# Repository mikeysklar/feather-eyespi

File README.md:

# feather-eyespi

A plus-size FeatherWing base board that accepts an Adafruit Feather and breaks out an EYESPI connector for eInk and TFT displays.

Working with a lot of eInk and TFT displays means constantly re-wiring the EYESPI cable. This adapter cuts out that step — plug the Feather in, plug the display in, done. Single-sided board with minimal routing to keep assembly straightforward.

### BOM

| Part | Package | 
|------|---------|
| EYESPI | 18-pin FPC connector 
| headers | Female 2.54mm vertical SMT 
| Resistor, 0Ω | 0805 

### EYESPI Connected to eInk

---

### Assembled

---

### 18-pin FPC 

---

### Metal Business Card Stencil

---

### Finish PCB Silk / Mask Etched

---

### Wiring

| Feather Pin | Net | EYESPI Pin | Function |
|-------------|-----|-----------|----------|
| SCK | sck | 15 | SPI clock |
| MOSI | mosi | 14 | SPI data out |
| MISO | miso | 13 | SPI data in |
| D11 | rst | 11 | Reset |
| D10 | dc | 12 | Data / Command |
| D12 | busy | 3 | Busy / Ready |
| D9 | tcs | 10 | TCS chip select |
| 3V3 | 3v3 | 18 | 3.3V power |
| GND | gnd | 16 | Ground |

---

### Fiber Laser Etched PCB 

---

### Backside board ID

---

### KiCAD PCB

---

## License

This project is licensed under the GNU General Public License v3.0 — see the [LICENSE](LICENSE) file for details.

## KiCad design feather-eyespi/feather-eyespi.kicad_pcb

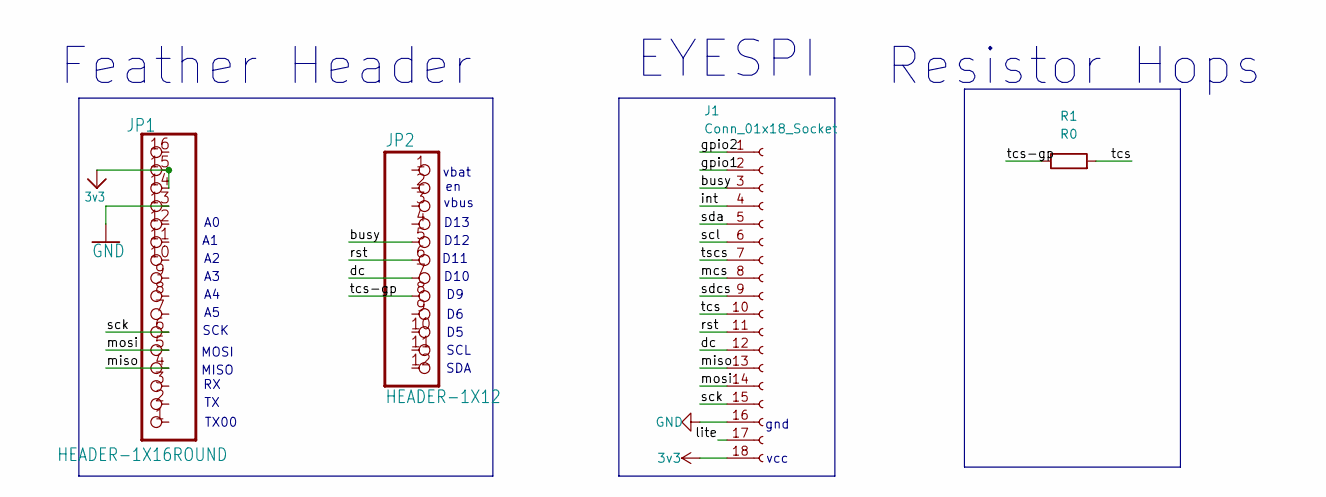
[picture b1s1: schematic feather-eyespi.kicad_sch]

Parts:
J1: Conn_01x18_Socket; Hirose_FH12-18S-0.5SH_1x18-1MP_P0.50mm_Horizontal
JP1: HEADER-1X16ROUND; PinHeader_1x16_P2.54mm_Vertical_SMD_Pin1Left
JP2: HEADER-1X12; PinSocket_1x12_P2.54mm_Vertical_SMD_Pin1Left
R1: R0; R_0805_2012Metric_Pad1.20x1.40mm_HandSolder

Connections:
3v3: J1.18, JP1.14, JP1.15
/busy: J1.3, JP2.5
/dc: J1.12, JP2.7
/gpio1: J1.2
/gpio2: J1.1
/int: J1.4
/lite: J1.17
/mcs: J1.8
/miso: J1.13, JP1.4
/mosi: J1.14, JP1.5
/rst: J1.11, JP2.6
/sck: J1.15, JP1.6
/scl: J1.6
/sda: J1.5
/sdcs: J1.9
/tcs: J1.10, R1.2
/tcs-gp: JP2.8, R1.1
/tscs: J1.7
GND: J1.16, JP1.13

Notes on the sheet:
SCK
D13
Resistor Hops
D12
D11
vcc
SCL
D10
vbus
Feather Header
SDA
vbat
gnd
TX00
MISO
EYESPI
MOSI

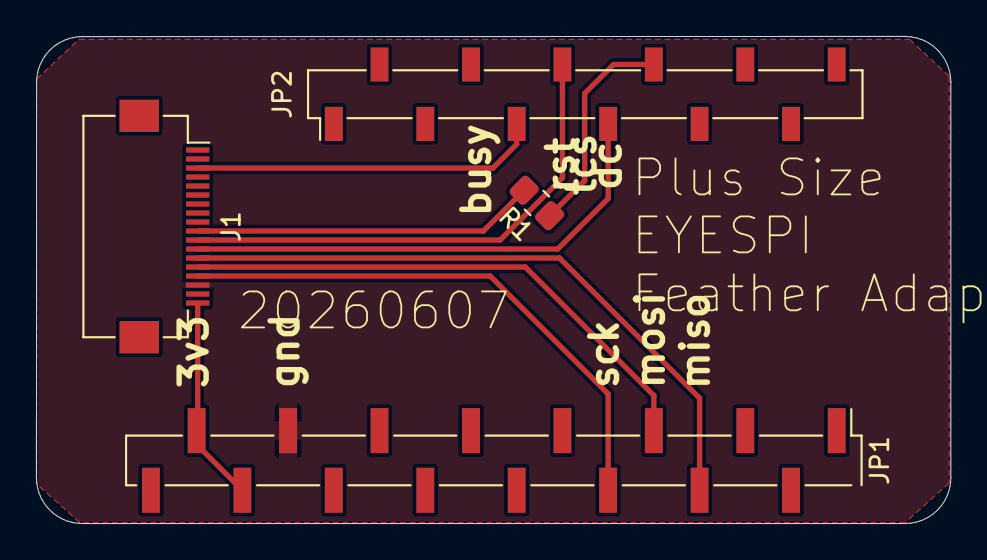
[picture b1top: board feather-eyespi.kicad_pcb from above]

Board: 2 copper layers, 50.8 x 27.1 mm, 4 parts (0 on the bottom side), 10 nets.
